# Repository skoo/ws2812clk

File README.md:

# ws2812clk
Clock with 60 WS2812 LEDs in circle.

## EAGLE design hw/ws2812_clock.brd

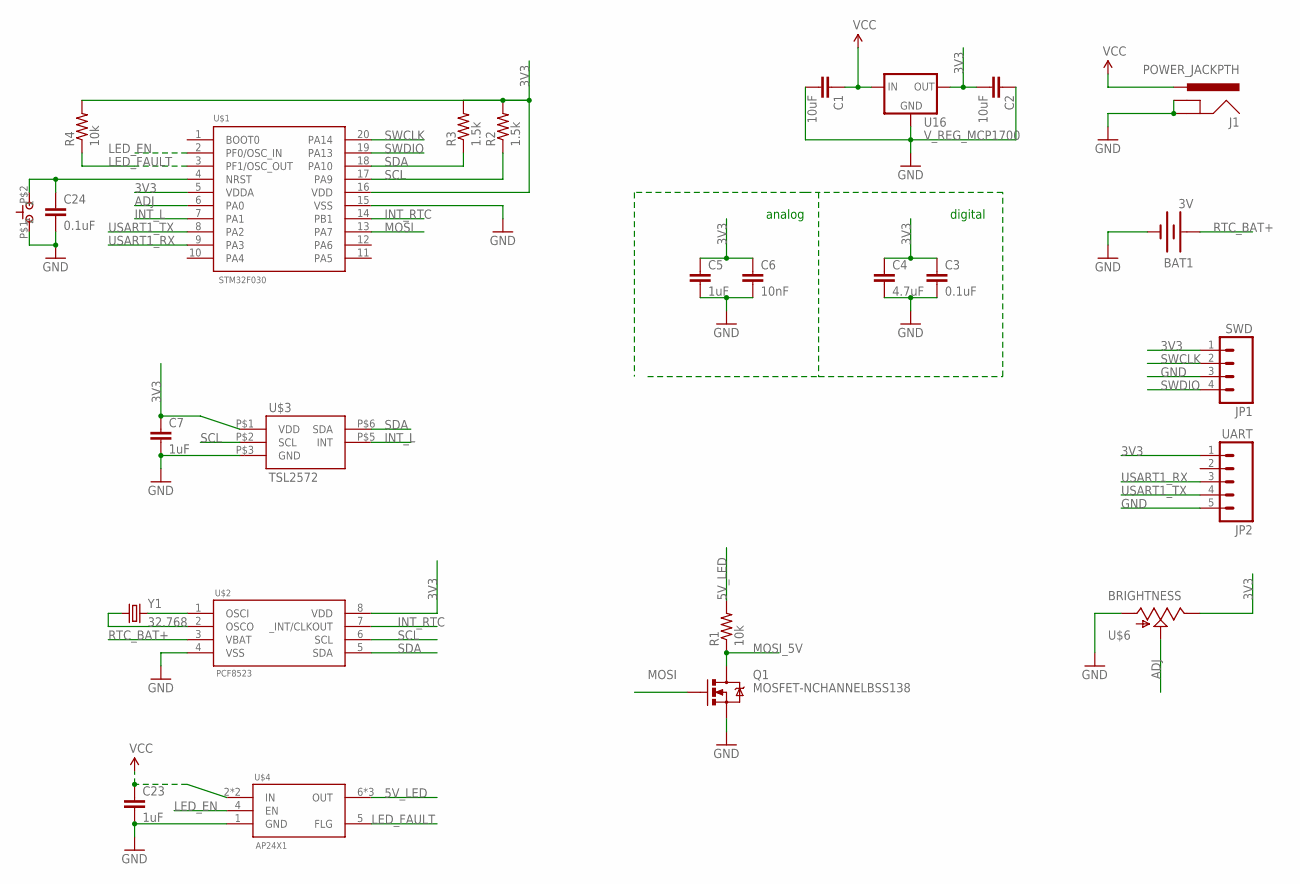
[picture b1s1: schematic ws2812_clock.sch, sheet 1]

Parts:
BAT1: 3V; BATTCON_12MM_PTH
C1, C2: 10uF; 0805
C3, C24: 0.1uF; 0603-CAP
C4: 4.7uF; 0805
C5, C7, C23: 1uF; 0805
C6: 10nF; 0603-CAP
J1: POWER_JACKPTH; POWER_JACK_PTH
JP1: SWD; 1X04
JP2: UART; 1X05
Q1: MOSFET-NCHANNELBSS138; SOT23
R1, R4: 10k; 0603-RES
R2, R3: 1.5k; 0603-RES
U16: V_REG_MCP1700; SOT23-3
U$1: STM32F030; TSSOP20
U$2: PCF8523; SO08
U$3: TSL2572; FN-6
U$4: AP24X1; MSOP8
U$5: TACTILE-SWITCH; 6X3.5
U$6: BRIGHTNESS; TRIM_POT
Y1: 32.768; CRYSTAL-CITIZEN

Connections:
3V3: C2.2, C3.1, C4.1, C5.1, C6.1, C7.1, JP1.1, JP2.1, R2.2, R3.2, R4.2, U16.2 (OUT), U$1.5 (VDDA), U$1.16 (VDD), U$2.8 (VDD), U$3.P$1 (VDD), U$6.2 (E)
5V_LED: R1.2, U$4.6 (OUT), U$4.7 (OUT), U$4.8 (OUT); also elsewhere on the board
ADJ: U$1.6 (PA0), U$6.1 (S)
GND: BAT1.GND (-), C1.2, C2.1, C3.2, C4.2, C5.2, C6.2, C7.2, C23.2, C24.2, J1.GND, J1.GNDBREAK, JP1.3, JP2.5, Q1.2 (S), U16.1 (GND), U$1.15 (VSS), U$2.4 (VSS), U$3.P$3 (GND), U$4.1 (GND), U$5.P$1 (1), U$6.3 (A); also elsewhere on the board
INT_L: U$1.7 (PA1), U$3.P$5 (INT)
INT_RTC: U$1.14 (PB1), U$2.7 (_INT/CLKOUT)
LED_EN: U$1.2 (PF0/OSC_IN), U$4.4 (EN)
LED_FAULT: R4.1, U$1.3 (PF1/OSC_OUT), U$4.5 (FLG)
MOSI: Q1.1 (G), U$1.13 (PA7)
MOSI_5V: Q1.3 (D), R1.1; also elsewhere on the board
unnamed: U$2.1 (OSCI), Y1.P$2 (2)
unnamed: U$2.2 (OSCO), Y1.P$1 (1)
unnamed: C24.1, U$1.4 (NRST), U$5.P$2 (2)
RTC_BAT+: BAT1.VCC@1 (+), U$2.3 (VBAT)
SCL: R2.1, U$1.17 (PA9), U$2.6 (SCL), U$3.P$2 (SCL)
SDA: R3.1, U$1.18 (PA10), U$2.5 (SDA), U$3.P$6 (SDA)
SWCLK: JP1.2, U$1.20 (PA14)
SWDIO: JP1.4, U$1.19 (PA13)
USART1_RX: JP2.3, U$1.9 (PA3)
USART1_TX: JP2.4, U$1.8 (PA2)
VCC: C1.1, C23.1, J1.PWR, U16.3 (IN), U$4.2 (IN), U$4.3 (IN)

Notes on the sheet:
analog
digital

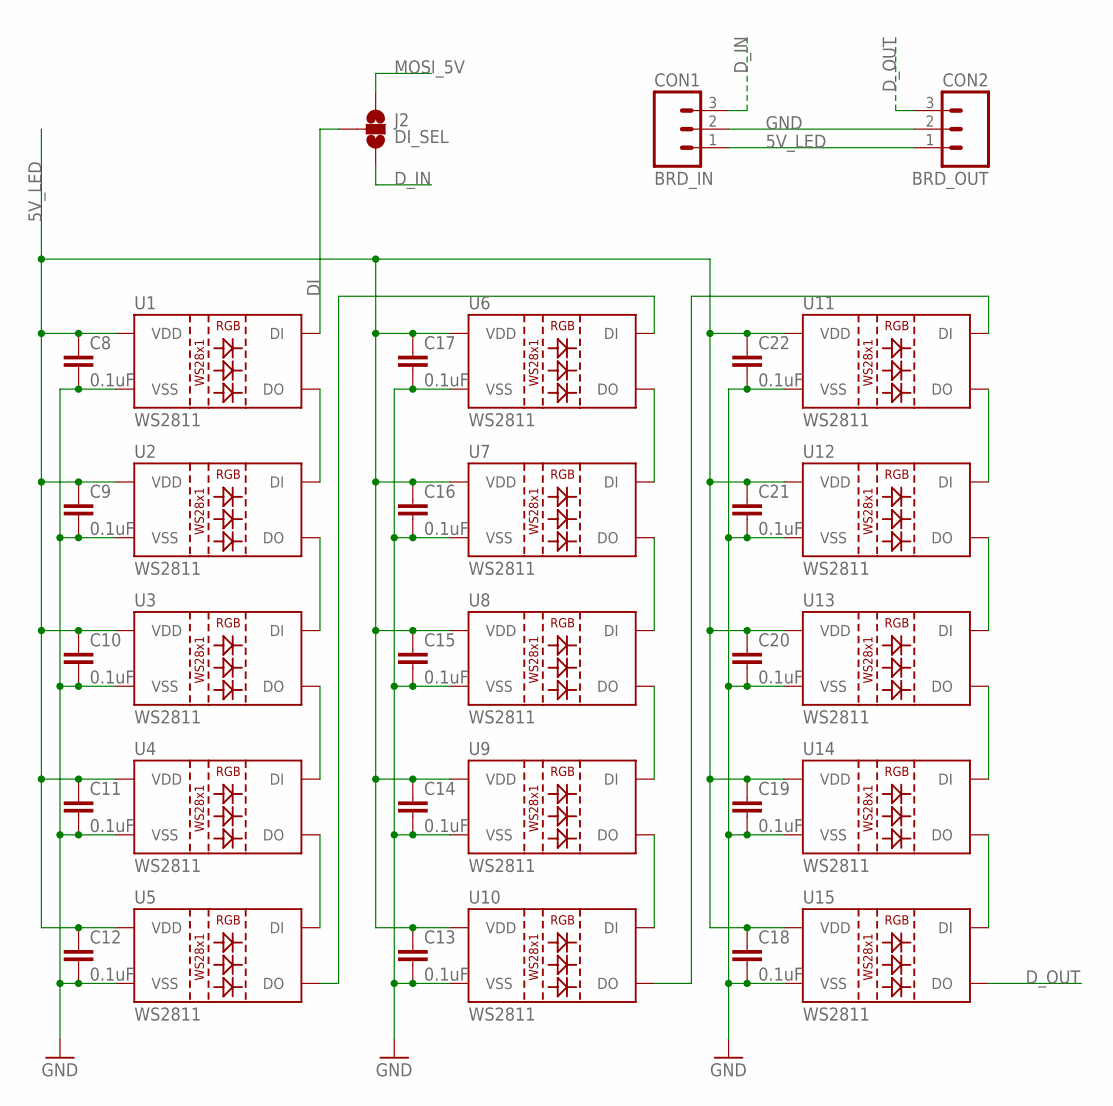
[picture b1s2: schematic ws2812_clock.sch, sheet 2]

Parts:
C8, C9, C10, C11, C12, C13, C14, C15, C16, C17, C18, C19, C20, C21, C22: 0.1uF; 0603-CAP
CON1: BRD_IN; 1X03
CON2: BRD_OUT; 1X03
J2: DI_SEL; SJ_2
U1, U2, U3, U4, U5, U6, U7, U8, U9, U10, U11, U12, U13, U14, U15: WS2811; LED-TRICOLOR-5050-IC

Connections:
5V_LED: C8.1, C9.1, C10.1, C11.1, C12.1, C13.1, C14.1, C15.1, C16.1, C17.1, C18.1, C19.1, C20.1, C21.1, C22.1, CON1.1, CON2.1, U1.3 (VDD), U1.5 (VDD), U2.3 (VDD), U2.5 (VDD), U3.3 (VDD), U3.5 (VDD), U4.3 (VDD), U4.5 (VDD), U5.3 (VDD), U5.5 (VDD), U6.3 (VDD), U6.5 (VDD), U7.3 (VDD), U7.5 (VDD), U8.3 (VDD), U8.5 (VDD), U9.3 (VDD), U9.5 (VDD), U10.3 (VDD), U10.5 (VDD), U11.3 (VDD), U11.5 (VDD), U12.3 (VDD), U12.5 (VDD), U13.3 (VDD), U13.5 (VDD), U14.3 (VDD), U14.5 (VDD), U15.3 (VDD), U15.5 (VDD); also elsewhere on the board
DI: J2.2, U1.2 (DI)
D_IN: CON1.3, J2.3
D_OUT: CON2.3, U15.1 (DO)
GND: C8.2, C9.2, C10.2, C11.2, C12.2, C13.2, C14.2, C15.2, C16.2, C17.2, C18.2, C19.2, C20.2, C21.2, C22.2, CON1.2, CON2.2, U1.6 (VSS), U2.6 (VSS), U3.6 (VSS), U4.6 (VSS), U5.6 (VSS), U6.6 (VSS), U7.6 (VSS), U8.6 (VSS), U9.6 (VSS), U10.6 (VSS), U11.6 (VSS), U12.6 (VSS), U13.6 (VSS), U14.6 (VSS), U15.6 (VSS); also elsewhere on the board
MOSI_5V: J2.1; also elsewhere on the board
unnamed: U1.1 (DO), U2.2 (DI)
unnamed: U2.1 (DO), U3.2 (DI)
unnamed: U3.1 (DO), U4.2 (DI)
unnamed: U4.1 (DO), U5.2 (DI)
unnamed: U5.1 (DO), U6.2 (DI)
unnamed: U6.1 (DO), U7.2 (DI)
unnamed: U7.1 (DO), U8.2 (DI)
unnamed: U8.1 (DO), U9.2 (DI)
unnamed: U9.1 (DO), U10.2 (DI)
unnamed: U10.1 (DO), U11.2 (DI)
unnamed: U11.1 (DO), U12.2 (DI)
unnamed: U12.1 (DO), U13.2 (DI)
unnamed: U13.1 (DO), U14.2 (DI)
unnamed: U14.1 (DO), U15.2 (DI)

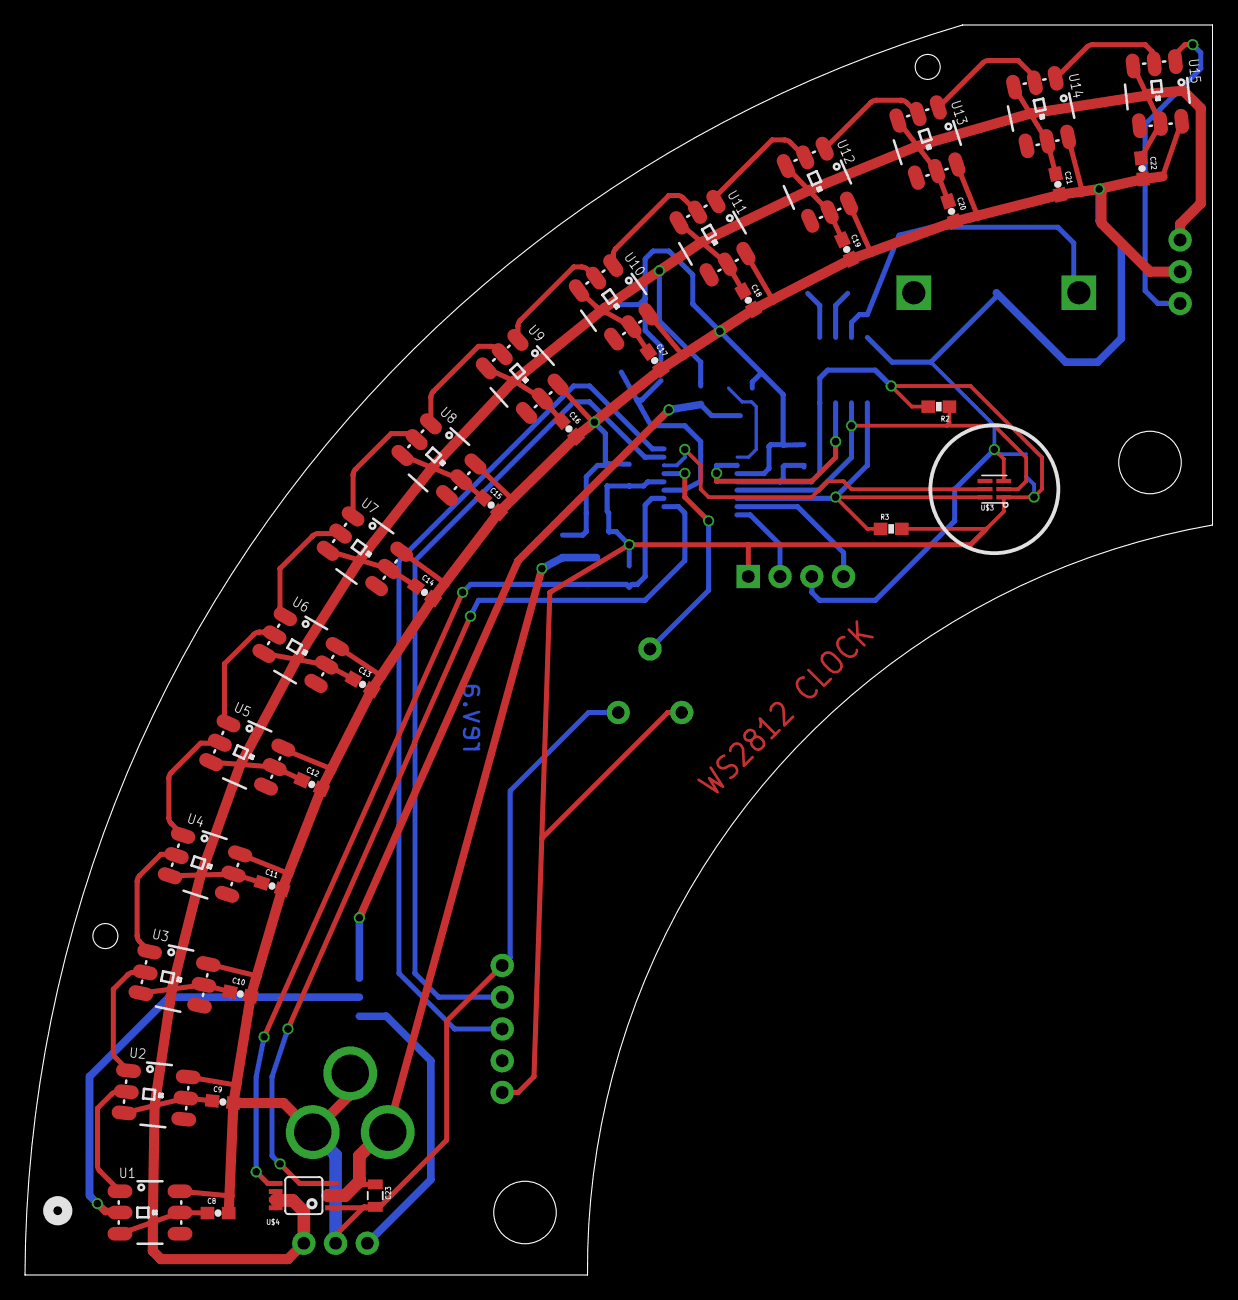
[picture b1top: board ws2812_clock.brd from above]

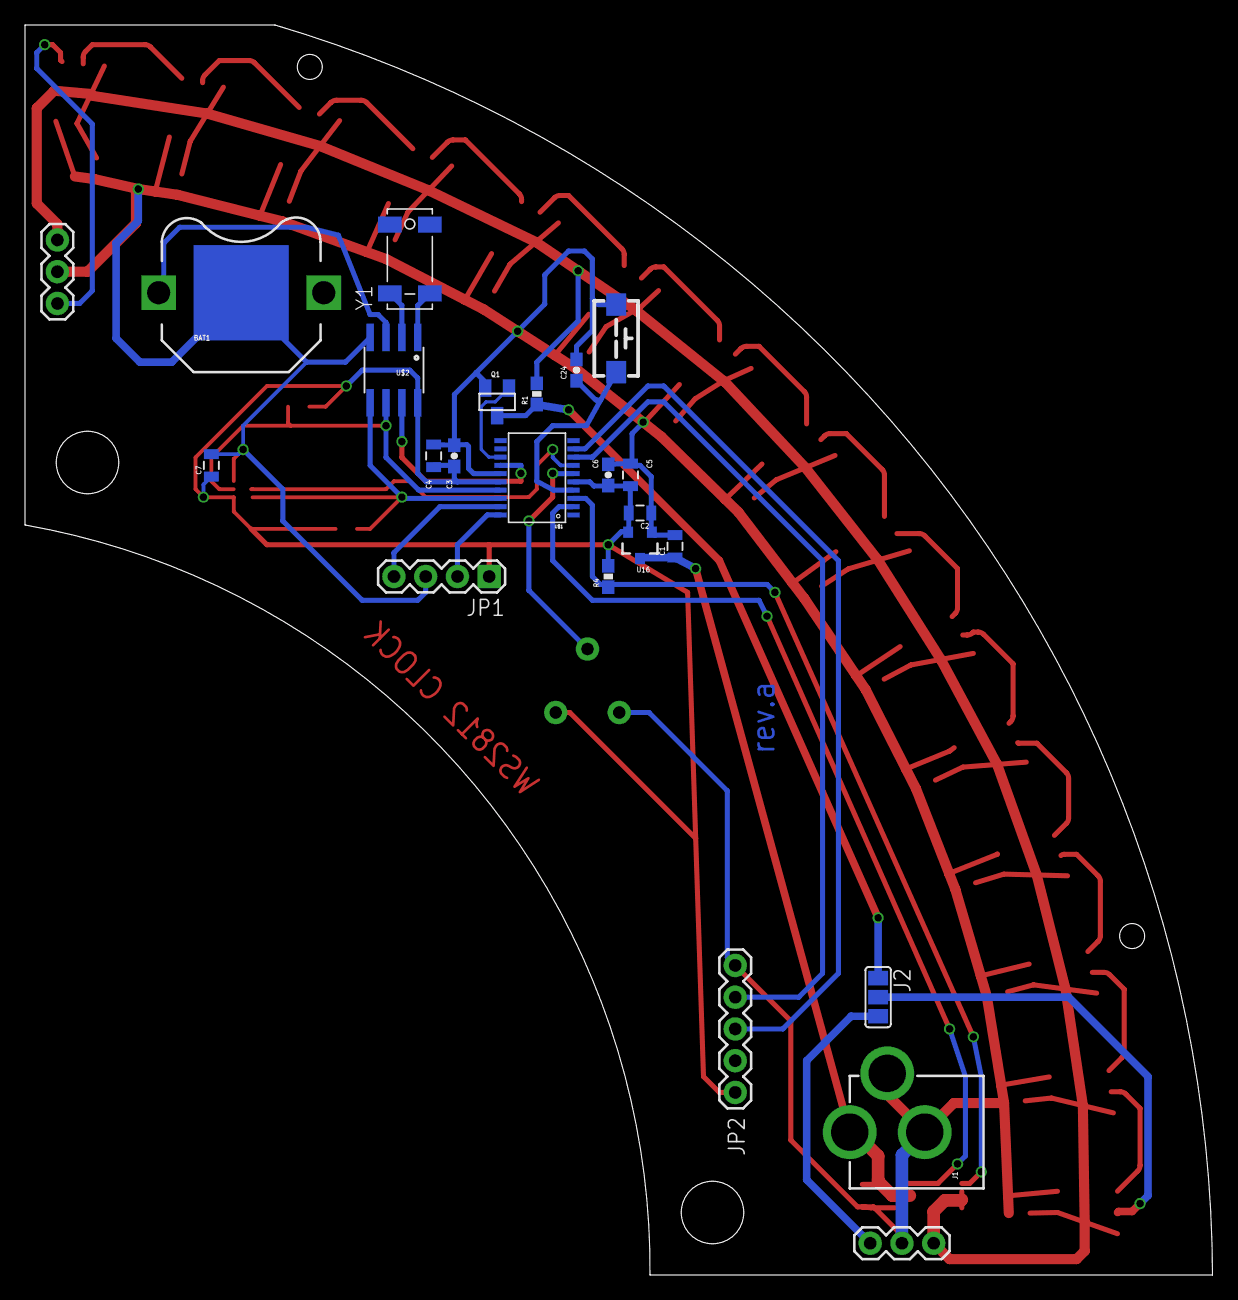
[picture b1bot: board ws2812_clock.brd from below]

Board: 2 copper layers, 95.0 x 100.0 mm, 59 parts (24 on the bottom side), 38 nets.

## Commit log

2016-07-05 Initial version.
2016-07-05 Android app for viewing clock setting web page
    Android app for viewing clock setting web page from github.io.
2016-07-09 Simpler clock face definition.
2016-07-09 Better brightness comparison for time programming.
2016-07-10 Fixed display update after clock time programming.

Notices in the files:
parts and their libraries:
SparkFun-LED: Licensing: CC v3.0 Share-Alike You are welcome to use this library for commercial purposes.
